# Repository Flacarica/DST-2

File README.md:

# The [DST-2](https://github.com/TudorSupica/DST-2/)

   The DST-2 is the second version of the DST distortion pedal series. Its main goal was to make the pedal much more modular and easier to debug, since I want all the future pedals to be compatible with one another. 
  
  The modularity comes from the use of JST connectors and modules like the [TMC-1](https://github.com/TudorSupica/TMC-1) and the [TMF](https://github.com/TudorSupica/TMF). These modules aim to standardise the pedal-making process and make all the future pedals compatible.

  The debugging aspect of the board comes from the use of test pads labeled accordingly, so that when a problem arises, it can be easily debugged and fixed. The test pads I added mainly target features like power supply and signal line. I also connected the four screw holes in the corners of the board to GND, so that when debugging I won’t have to look for a ground test point.

  Another feature that I introduced with this board is the use of SMD components rather than THT ones (except for a couple diodes and the transistors). This change aimed to minimize the board size, to ensure it is going to fit alongside the other modules in the metal enclosure.

  # [The Schematic](https://github.com/TudorSupica/DST-2/blob/main/Schematic/)
   The schematic is made up of a few blocks: a buffer stage, an initial amplifying stage, a variable gain stage, a clipping stage, a filtering stage, and a final buffer stage. 

   ### The buffer stage 
   The buffer stage is a voltage follower made up of the transistor *Q1* and *R1*, *R2* and *C1*, *C2*.
   
   This stage has a voltage gain of (*ideally*) 1, so that the voltage at the collector of *Q1* is exactly the signal but 180º out of phase (*basically the signal but inverted, lmao maths*). But the real advantage of the buffer stage comes from the high-impedance input and low-impedance output of the stage. 
  
   The resistor *R1* biases the transistor whilst the resistor *R2* provides thermal stability (*you **could** add another capacitor in parallel with R2, so that it shorts at higher frequencies providing better stability thus a better frequency response*). The capacitors *C1* and *C2* are decoupling capacitors. They eliminate the DC characteristic of the signal so that I can bias it however I need to (*again, lmao maths*).

   ### The initial amplifying stage
   The initial amplifying stage is made up of the transistor *Q2*, the resistors *R3* thru *R6* and the capacitors *C3* thru *C5*.

   The resistor *R3* and capacitor *C3* make up a high-pass filter with a cutoff frequency of about 33 Hz. The capacitor *C3* is also used to decouple the signal, and the resistor *R4* is used to bias the base signal of the transistor *Q2*.

   The resistor *R5* and the capacitor *C4* make up the feedback loop of the stage, whilst the resistor *R6* gives the amplifying ratio of the stage (*its ratio is roughly R6/internal resistance of the BE junction*).

   Finally, the capacitor *C5* is used to decouple the signal before it reaches the next stage.

   ### The variable gain stage
   The variable gain stage is made up of a few components, mainly a double op-amp SOIC-8 IC (*even tho the TL072 or the LM358 work fine, I'd strongly recommend some better op-amps such as the OPA2134*) with some support components such as resistors and capacitors.
  
   # [The PCB](https://github.com/TudorSupica/DST-2/blob/main/PCB/)
  Yappa yappa PCB yappa yappa type shi

   # After initial testing

After initial testing, the pedal seems to work but just barely. There is a whole lot of induced noise. The values for the filter are all over the place and make the pedal sound too muffled. Overall just a bad tone. I've since learned that JST connectors are really really unreliable and that the use of separate "modules" for the footswitch and the jack connectors is a bad idea. It adds complexity and are really really prone to failure / noise. I plan on redesigning it without all that fuss, one board to rule them all. The footswitch placement is still an issue tho. I can’t mount it directly on the PCB since I can’t reliably predict the final height of the whole assembly (it can be soldered higher or lower). Therefore, it needs to remain separate, with wires manually routed to it. The same applies to the jack connectors. The barrel connector on the other hand, i can have it on the PCB no problem since it needs some stability to work properly. The potentiometers need to be routed manually also.

   ## Conclusions:
-new pcb
-manually route wires to pots/conns/switch
-change filter values
-pick another IC for the board (OPA2134)

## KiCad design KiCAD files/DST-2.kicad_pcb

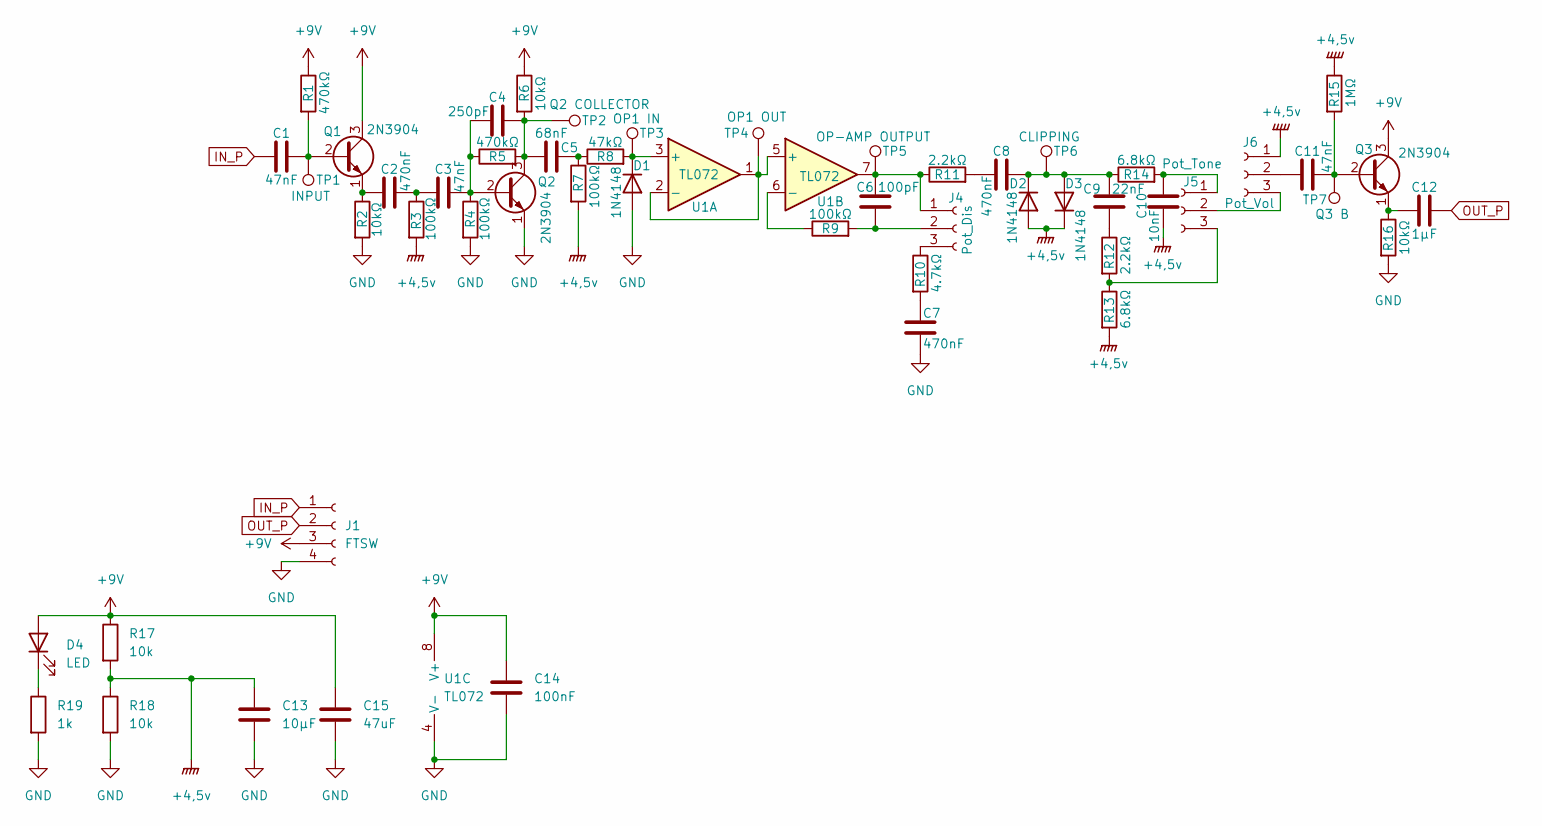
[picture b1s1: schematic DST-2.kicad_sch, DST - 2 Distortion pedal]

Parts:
C1, C3, C11: 47nF; C_0603_1608Metric_Pad1.08x0.95mm_HandSolder
C2, C7, C8: 470nF; C_0603_1608Metric_Pad1.08x0.95mm_HandSolder
C4: 250pF; C_0603_1608Metric_Pad1.08x0.95mm_HandSolder
C5: 68nF; C_0603_1608Metric_Pad1.08x0.95mm_HandSolder
C6: 100pF; C_0603_1608Metric_Pad1.08x0.95mm_HandSolder
C9: 22nF; C_0603_1608Metric_Pad1.08x0.95mm_HandSolder
C10: 10nF; C_0603_1608Metric_Pad1.08x0.95mm_HandSolder
C12: 1µF; C_0603_1608Metric_Pad1.08x0.95mm_HandSolder
C13: 10µF; C_Radial_D5.0mm_H11.0mm_P2.00mm
C14: 100nF; C_0603_1608Metric_Pad1.08x0.95mm_HandSolder
C15: 47uF; C_Radial_D5.0mm_H11.0mm_P2.00mm
D1, D2, D3: 1N4148; D_SOD-323F
D4: LED; LED_D5.0mm
J1: FTSW; PinHeader_1x04_P2.54mm_Vertical
J4: Pot_Dis; PinHeader_1x03_P2.54mm_Vertical
J5: Pot_Tone; PinHeader_1x03_P2.54mm_Vertical
J6: Pot_Vol; PinHeader_1x03_P2.54mm_Vertical
Q1, Q2, Q3: 2N3904; TSOT-23_HandSoldering
R1, R5: 470kΩ; R_0603_1608Metric_Pad0.98x0.95mm_HandSolder
R2, R6, R16: 10kΩ; R_0603_1608Metric_Pad0.98x0.95mm_HandSolder
R3, R4, R7, R9: 100kΩ; R_0603_1608Metric_Pad0.98x0.95mm_HandSolder
R8: 47kΩ; R_0603_1608Metric_Pad0.98x0.95mm_HandSolder
R10: 4.7kΩ; R_0603_1608Metric_Pad0.98x0.95mm_HandSolder
R11, R12: 2.2kΩ; R_0603_1608Metric_Pad0.98x0.95mm_HandSolder
R13, R14: 6.8kΩ; R_0603_1608Metric_Pad0.98x0.95mm_HandSolder
R15: 1MΩ; R_0603_1608Metric_Pad0.98x0.95mm_HandSolder
R17, R18: 10k; R_0603_1608Metric_Pad0.98x0.95mm_HandSolder
R19: 1k; R_0603_1608Metric_Pad0.98x0.95mm_HandSolder
TP1: INPUT; TestPoint_Pad_D1.0mm
TP2: Q2 COLLECTOR; TestPoint_Pad_D1.0mm
TP3: OP1 IN; TestPoint_Pad_D1.0mm
TP4: OP1 OUT; TestPoint_Pad_D1.0mm
TP5: OP-AMP OUTPUT; TestPoint_Pad_D1.0mm
TP6: CLIPPING; TestPoint_Pad_D1.0mm
TP7: Q3 B; TestPoint_Pad_D1.0mm
U1: TL072; SOIC-8_5.3x5.3mm_P1.27mm

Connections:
+4,5v: C10.1, C13.1, D2.2 (A), D3.1 (K), J6.1, R3.2, R7.2, R13.2, R15.1, R17.2, R18.1
+9V: C14.1, C15.1, D4.2 (A), J1.3, Q1.3 (C), Q3.3 (C), R1.1, R6.1, R17.1, U1.8 (V+)
GND: C7.2, C13.2, C14.2, C15.2, D1.2 (A), J1.4, Q2.1 (E), R2.2, R4.2, R16.2, R18.2, R19.2, U1.4 (V-)
IN_P: C1.1, J1.1
unnamed: C2.2, C3.1, R3.1
unnamed: C5.2, R7.1, R8.1
unnamed: C7.1, R10.2
unnamed: C8.1, R11.2
unnamed: C9.2, R12.1
unnamed: D1.1 (K), R8.2, TP3.1 (1_1), U1.3 (+)
unnamed: C8.2, C9.1, D2.1 (K), D3.2 (A), R14.1, TP6.1 (1_1)
unnamed: D4.1 (K), R19.1
unnamed: C6.1, J4.1, R11.1, TP5.1 (1_1), U1.7
unnamed: C6.2, J4.2, R9.2
unnamed: J4.3, R10.1
unnamed: C10.2, J5.1, R14.2
unnamed: J5.2, J6.3
unnamed: J5.3, R12.2, R13.1
unnamed: C11.1, J6.2
unnamed: C1.2, Q1.2 (B), R1.2, TP1.1 (1_1)
unnamed: C2.1, Q1.1 (E), R2.1
unnamed: C3.2, C4.1, Q2.2 (B), R4.1, R5.1
unnamed: C4.2, C5.1, Q2.3 (C), R5.2, R6.2, TP2.1 (1_1)
unnamed: C11.2, Q3.2 (B), R15.2, TP7.1 (1_1)
unnamed: C12.1, Q3.1 (E), R16.1
unnamed: TP4.1 (1_1), U1.1, U1.2 (-), U1.5 (+)
unnamed: R9.1, U1.6 (-)
OUT_P: C12.2, J1.2

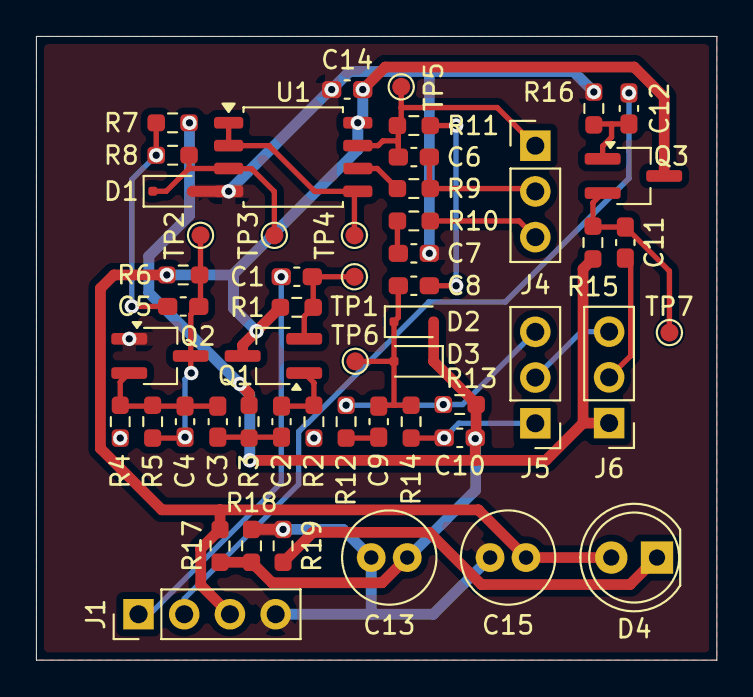
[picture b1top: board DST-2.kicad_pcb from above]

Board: 2 copper layers, 37.8 x 34.7 mm, 53 parts (0 on the bottom side), 28 nets.

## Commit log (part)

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2026-02-10 Update README with corrections and testing results
    Corrected typos and improved clarity in the README content. Added initial testing results and conclusions for the DST-2 pedal.
